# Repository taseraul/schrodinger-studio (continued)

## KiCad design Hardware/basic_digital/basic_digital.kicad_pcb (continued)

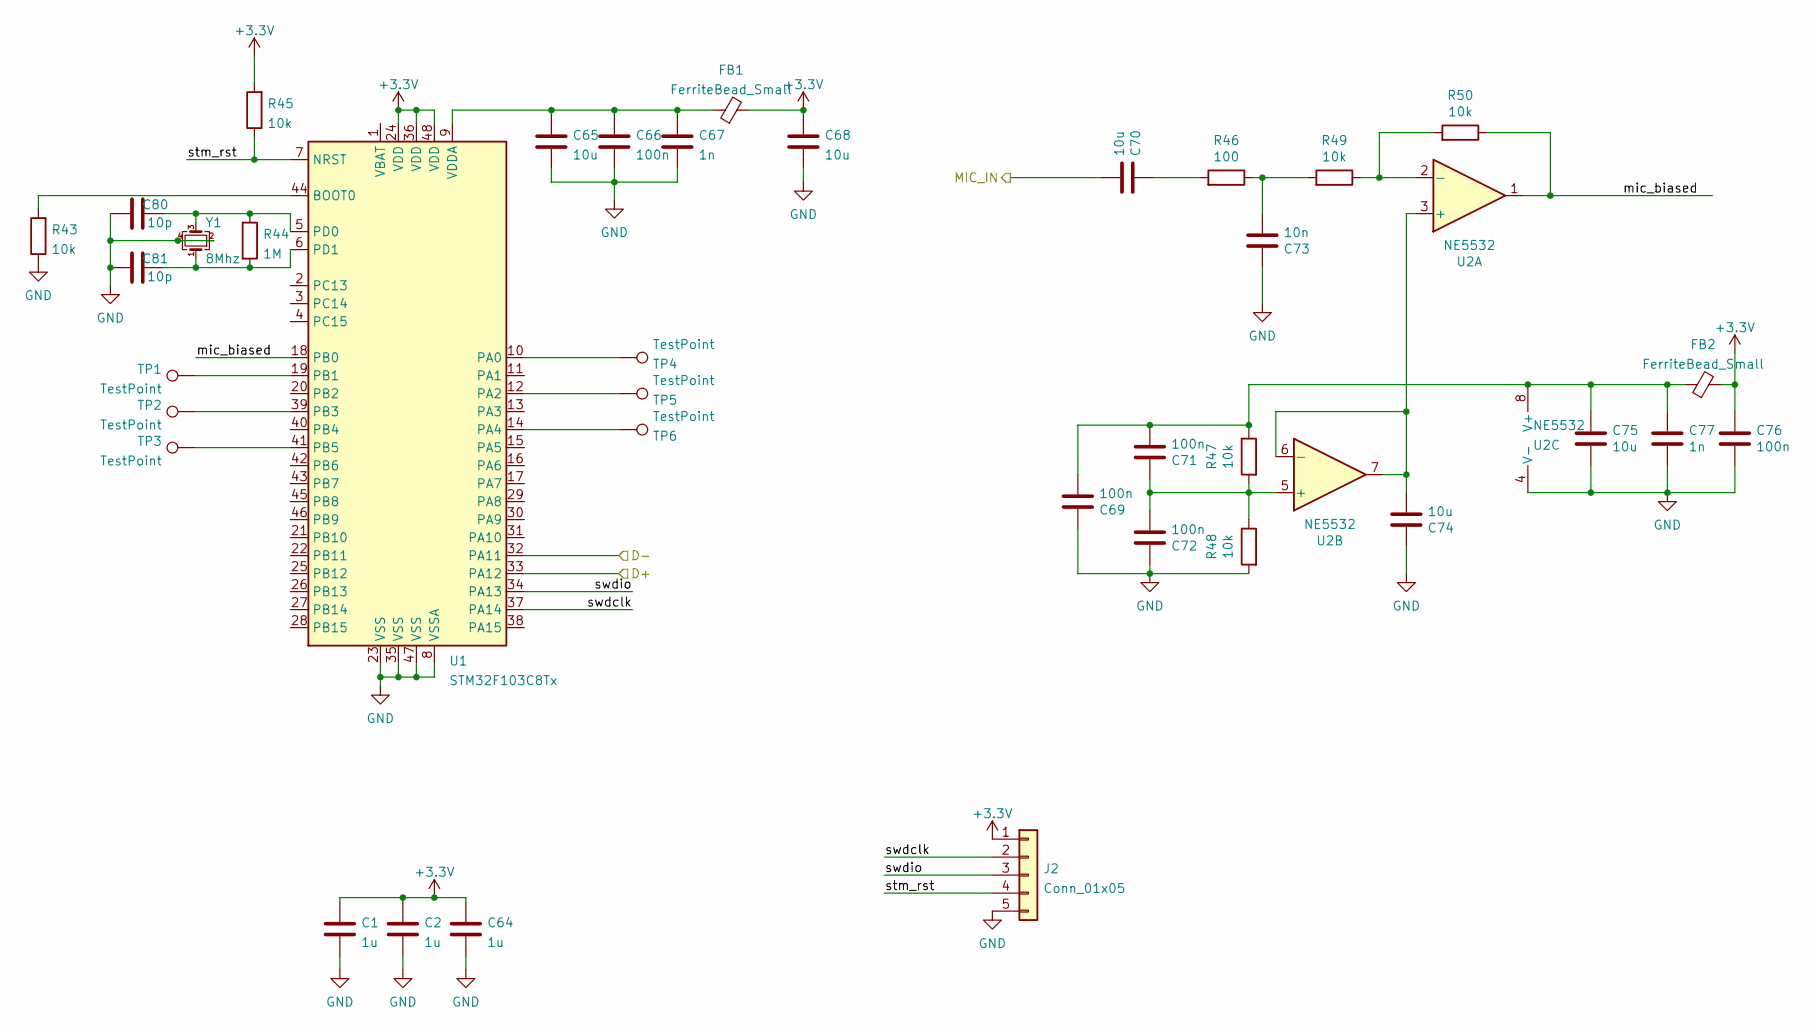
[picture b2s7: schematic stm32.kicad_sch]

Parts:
C1, C2, C64: 1u; C_0603_1608Metric
C65, C68, C70, C74, C75: 10u; C_0603_1608Metric
C66, C69, C71, C72, C76: 100n; C_0603_1608Metric
C67, C77: 1n; C_0603_1608Metric
C73: 10n; C_0603_1608Metric
C80, C81: 10p; C_0603_1608Metric
FB1, FB2: FerriteBead_Small; C_0805_2012Metric
J2: Conn_01x05; PinHeader_1x05_P2.54mm_Vertical
R43, R45, R47, R48, R49, R50: 10k; R_0603_1608Metric
R44: 1M; R_0603_1608Metric
R46: 100; R_0603_1608Metric
TP1, TP2, TP3, TP4, TP5, TP6: TestPoint; TestPoint_Pad_D1.0mm
U1: STM32F103C8Tx; LQFP-48_7x7mm_P0.5mm
U2: NE5532; SOIC-8_3.9x4.9mm_P1.27mm
Y1: 8Mhz; Crystal_SMD_3225-4Pin_3.2x2.5mm

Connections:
+3V3: C1.1, C2.1, C64.1, C68.1, C76.1, FB1.2, FB2.2, J2.1, R45.2, U1.24 (VDD), U1.36 (VDD), U1.48 (VDD); also elsewhere on the board
/power/D+: U1.33 (PA12); also elsewhere on the board
/power/D-: U1.32 (PA11); also elsewhere on the board
/side_con/IN_MONO: C70.2; also elsewhere on the board
/stm32/mic_biased: R50.1, U1.18 (PB0), U2.1
/stm32/stm_rst: J2.4, R45.1, U1.7 (NRST)
/stm32/swdclk: J2.2, U1.37 (PA14)
/stm32/swdio: J2.3, U1.34 (PA13)
unnamed: C65.1, C66.1, C67.1, FB1.1, U1.9 (VDDA)
unnamed: C69.2, C71.2, C75.1, C77.1, FB2.1, R47.1, U2.8 (V+)
unnamed: C70.1, R46.2
unnamed: C71.1, C72.2, R47.2, R48.1, U2.5 (+)
unnamed: C73.2, R46.1, R49.2
unnamed: C74.2, U2.3 (+), U2.6 (-), U2.7
unnamed: C80.2, R44.1, U1.5 (PD0), Y1.3
unnamed: C81.2, R44.2, U1.6 (PD1), Y1.1
unnamed: R43.2, U1.44 (BOOT0)
unnamed: R49.1, R50.2, U2.2 (-)
unnamed: TP1.1, U1.19 (PB1)
unnamed: TP2.1, U1.39 (PB3)
unnamed: TP3.1, U1.41 (PB5)
unnamed: TP4.1, U1.10 (PA0)
unnamed: TP5.1, U1.12 (PA2)
unnamed: TP6.1, U1.14 (PA4)

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
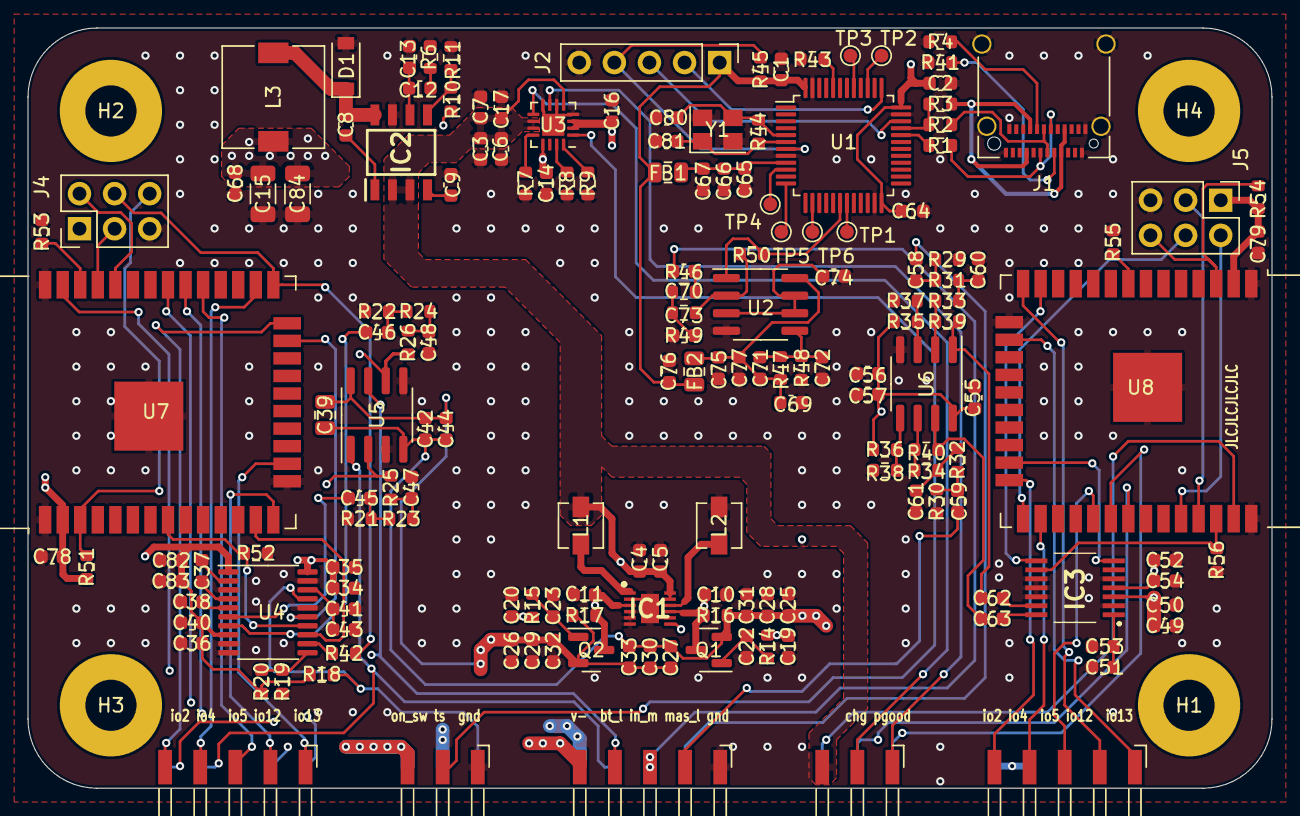
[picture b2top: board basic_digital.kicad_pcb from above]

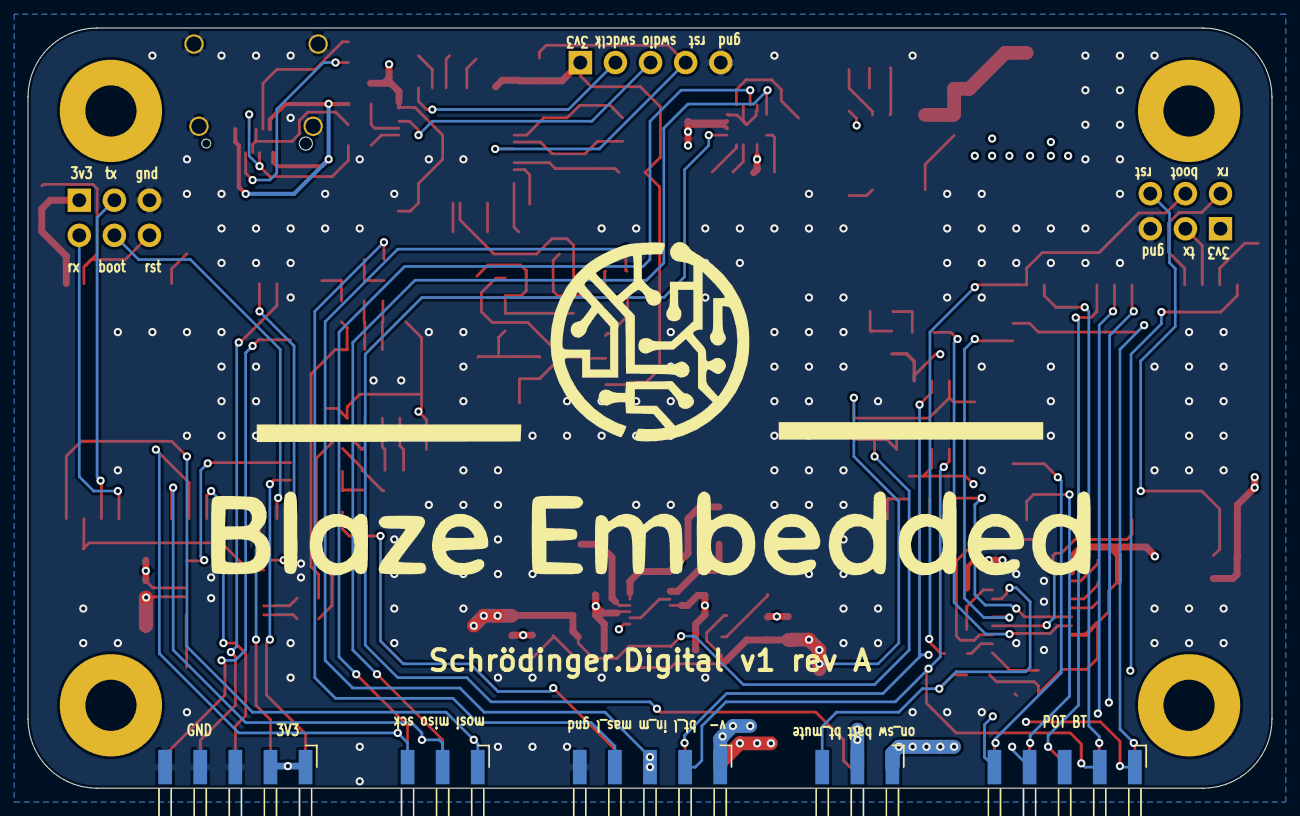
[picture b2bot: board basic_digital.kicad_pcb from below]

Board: 4 copper layers, 90.0 x 55.0 mm, 176 parts (5 on the bottom side), 114 nets.

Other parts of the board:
C78: 1u; C_0603_1608Metric
J4: Conn_01x06; PinHeader_2x03_P2.54mm_Vertical
J9: Conn_01x05; Harwin_M20-89005xx_1x05_P2.54mm_Horizontal
R51: 10k; R_0603_1608Metric
R52, R53: 100k/NC; R_0603_1608Metric
U7: ESP32-WROOM-32

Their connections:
+3V3: C78.1, J4.1, R51.2, U7.2 (VDD); also elsewhere on the board
/bt_in/BCK: U7.13 (IO14); also elsewhere on the board
/bt_in/I2S_IN: R53.2, U7.36 (IO22)
/bt_in/I2S_OUT: R52.2, U7.8 (IO32); also elsewhere on the board
/bt_in/MISO: U7.31 (IO19); also elsewhere on the board
/bt_in/MOSI: U7.37 (IO23); also elsewhere on the board
/bt_in/SCK: U7.30 (IO18); also elsewhere on the board
/bt_in/WS: U7.23 (IO15); also elsewhere on the board
/bt_in/boot: J4.4, U7.25 (IO0); also elsewhere on the board
/bt_in/cs1: J9.3, U7.29 (IO5)
/bt_in/cs2: J9.4, U7.26 (IO4)
/bt_in/io2: J9.5, U7.24 (IO2)
/bt_in/io12: J9.2, U7.14 (IO12)
/bt_in/io13: J9.1, U7.16 (IO13)
/bt_in/rst: J4.6, R51.1, U7.3 (EN)
/bt_in/rx: J4.2, U7.34 (RXD0/IO3)
/bt_in/tx: J4.3, U7.35 (TXD0/IO1)

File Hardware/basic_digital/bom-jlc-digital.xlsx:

Id | Designator | Package | Quantity | Designation | Supplier and ref | Column1 | _1
2 | FB2,FB1 | C_0805_2012Metric | C1017 | FerriteBead_Small
3 | R23,R24,R31,R32,R46 | R_0603_1608Metric | C22775 | 100
4 | C52,C20,C25,C45,C5,C34,C3,C74,C26,C82,C59,C68,C75,C23,C27,C58,C70,C65,C51,C63,C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 | C_0603_1608Metric | C96446 | 10u
6 | U4 | TSSOP-20_4.4x6.5mm_P0.65mm | C107671 | PCM5102
7 | C7,C44,C77,C31,C33,C57,C32,C67 | C_0603_1608Metric | C1588 | 1n
8 | C73,C61,C60,C9,C48,C47 | C_0603_1608Metric | C57112 | 10n
9 | U7,U8 | ESP32-WROOM-32 | C473012 | ESP32-WROOM-32
10 | R34,R40,R54,R37,R33,R43,R35,R18,R48,R51,R39,R45,R10,R47,R49,R36,R38,R50 | R_0603_1608Metric | C25804 | 10k
12 | R52,R56,R55,R53 | C23345 | C23345 | 100k/NC
13 | Q2 | SOT-23 | 1 | BC849
14 | C39 | C_0805_2012Metric | C15850 | 10u/25v
15 | C41,C35,C36,C54,C53,C83,C50 | C_0603_1608Metric | C14663 | 0.1u
16 | Y1 | Crystal_SMD_3225-4Pin_3.2x2.5mm | C242217 | 8Mhz
18 | D1 | D_SOD-123 | C8598 | D_Schottky
20 | R30,R29,R22,R21 | R_0603_1608Metric | C22961 | 220k
21 | Q1 | SOT-23 | 1 | MMBT4403
22 | L1,L2 | L_Vishay_IHLP-1212 | C354574 | 4.7u
23 | C14,C78,C64,C79,C16,C1,C17,C2 | C_0603_1608Metric | C15849 | 1u
24 | R1,R2 | R_0603_1608Metric | C23345 | 20R
25 | C66,C72,C69,C76,C8,C28,C6,C56,C42,C30,C29,C71 | C_0603_1608Metric | C14663 | 100n
26 | IC3 | PCM1808PWR | C55513 | PCM1808PWR
27 | R41,R4,R26,R25 | R_0603_1608Metric | C23186 | 5.1k
29 | U1 | LQFP-48_7x7mm_P0.5mm | 1 | STM32F103C8Tx
30 | R11 | R_0603_1608Metric | C22978 | 3.3k
31 | C37,C38 | C_0603_1608Metric | C23630 | 2.2u
32 | R14,R15 | R_0603_1608Metric | C25819 | 47k
33 | IC1 | SON45P300X300X80-13N-D | C134100 | TPS65133DPDR
34 | R17,R42,R8,R16,R19 | R_0603_1608Metric | C21189 | 0
35 | C15,C84 | C_1206_3216Metric | C96123 | 47u
37 | R6 | R_0603_1608Metric | C22974 | 29.4k
38 | U5,U2,U6 | SOIC-8_3.9x4.9mm_P1.27mm | C7426 | NE5532
39 | R3 | R_0603_1608Metric | C23162 | 4.7k
42 | R44 | R_0603_1608Metric | C22935 | 1M
43 | C12 | C_0603_1608Metric | C1588 | 1000p
44 | L3 | L_7.3x7.3_H4.5 | C354608 | 6.8u
45 | IC2 | SOIC127P600X175-8N | C9865 | TPS54331DR
46 | U3 | VQFN-16-1EP_3x3mm_P0.5mm_EP1.6x1.6mm | C140288 | BQ24072RGT
47 | C13 | C_0603_1608Metric | C1669 | 4.7p
48 | C81,C80 | C_0603_1608Metric | C1634 | 10p
49 | R9,R7 | R_0603_1608Metric | C22975 | 2k
50 | R20 | R_0603_1608Metric | 1 | NC

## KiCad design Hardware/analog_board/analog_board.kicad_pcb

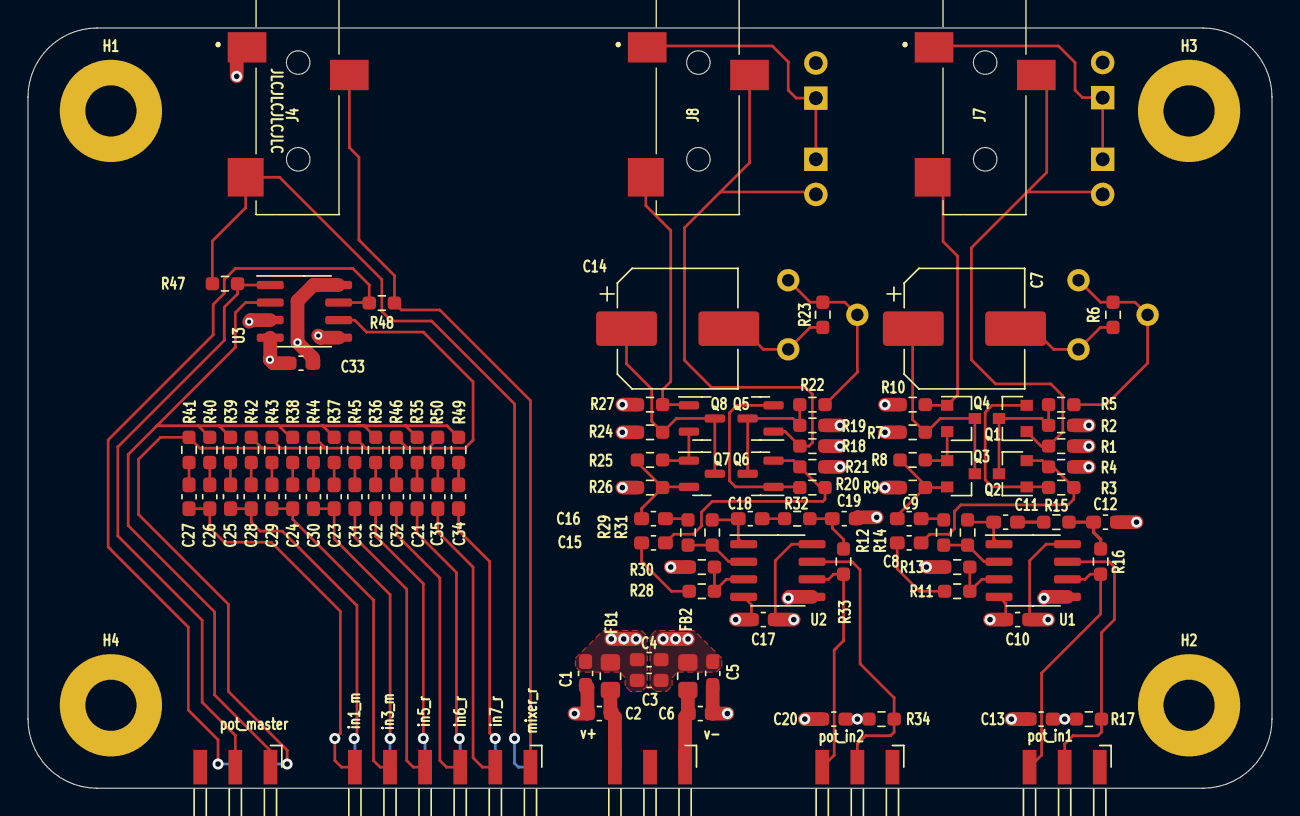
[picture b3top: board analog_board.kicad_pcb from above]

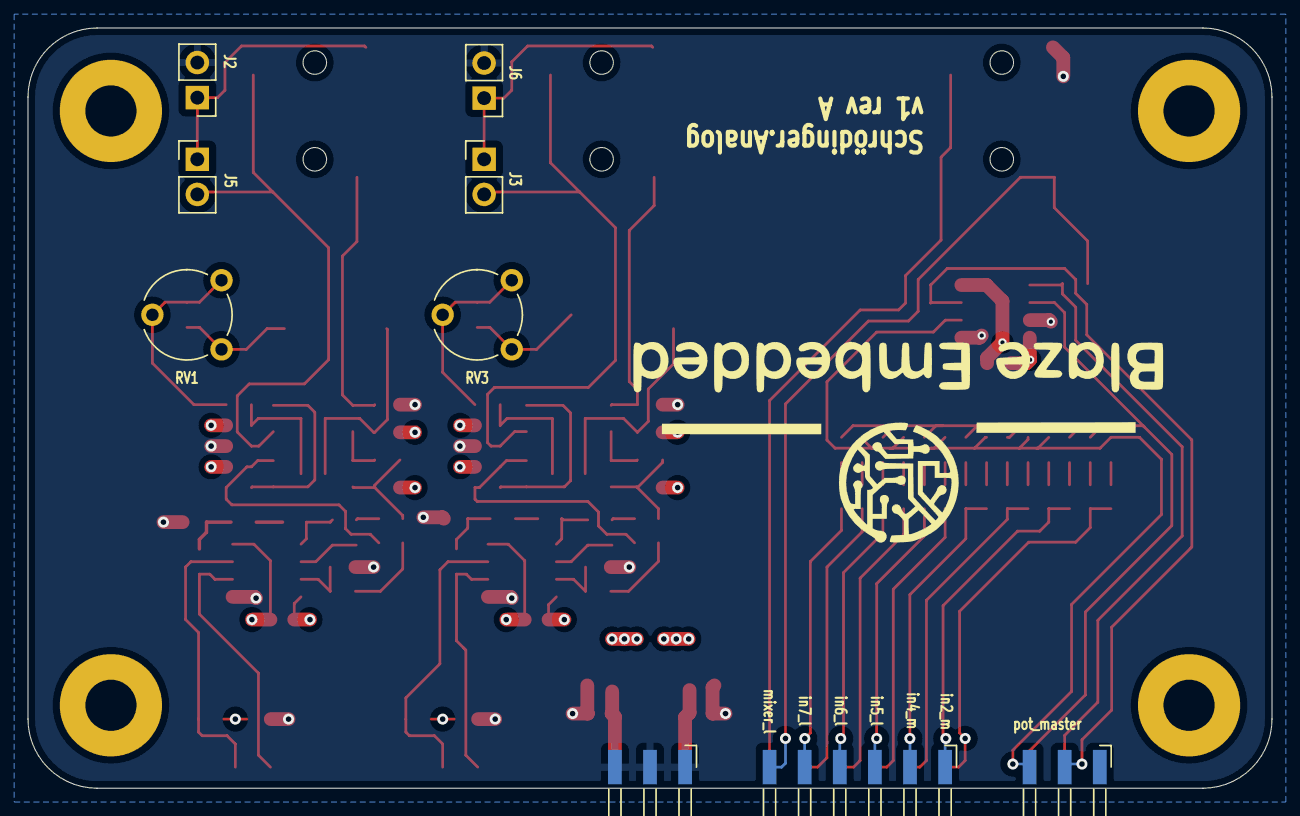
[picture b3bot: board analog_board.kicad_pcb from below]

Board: 4 copper layers, 90.0 x 55.0 mm, 119 parts (9 on the bottom side), 75 nets.

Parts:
C1, C2, C3, C5, C6, C8, C9, C10, C15, C16, C17, C21, C22, C23, C24, C25, C26, C27, C28, C29, C30, C31, C32, C33, C34, C35: 10u; C_0603_1608Metric_Pad1.08x0.95mm_HandSolder
C4: 100n; C_0603_1608Metric_Pad1.08x0.95mm_HandSolder
C7, C14: 1000u; CP_Elec_8x10.5
C11, C18: 1u; C_0603_1608Metric_Pad1.08x0.95mm_HandSolder
C12, C13, C19, C20: 10n; C_0603_1608Metric_Pad1.08x0.95mm_HandSolder
FB1, FB2: FerriteBead_Small; R_0805_2012Metric_Pad1.20x1.40mm_HandSolder
H1, H2, H3, H4: MountingHole_Pad; MountingHole_3.7mm_Pad
J1, J9: Conn_01x06; Harwin_M20-89006xx_1x06_P2.54mm_Horizontal
J2, J3, J5, J6: Conn_01x02; PinHeader_1x02_P2.54mm_Vertical
J4, J7, J8: SJ-3523-SMT-TR; SJ3523SMTTR
J10, J11: Conn_01x03; Harwin_M20-89003xx_1x03_P2.54mm_Horizontal
Q1, Q4, Q5, Q8: MMBT4403; SOT-23
Q2, Q3, Q6, Q7: BC849; SOT-23
R1, R10, R16, R18, R27, R33: 3.3k; R_0603_1608Metric_Pad0.98x0.95mm_HandSolder
R2, R7, R19, R24: 4.7k; R_0603_1608Metric_Pad0.98x0.95mm_HandSolder
R3, R8, R15, R17, R20, R25, R32, R34: 680; R_0603_1608Metric_Pad0.98x0.95mm_HandSolder
R4, R9, R21, R26: 2.2k; R_0603_1608Metric_Pad0.98x0.95mm_HandSolder
R5, R22: 22; R_0603_1608Metric_Pad0.98x0.95mm_HandSolder
R6, R13, R14, R23, R30, R31: 100k; R_0603_1608Metric_Pad0.98x0.95mm_HandSolder
R11, R12, R28, R29: 22k; R_0603_1608Metric_Pad0.98x0.95mm_HandSolder
R35, R36, R37, R38, R39, R40, R41, R42, R43, R44, R45, R46, R49, R50: 5.1k; R_0603_1608Metric_Pad0.98x0.95mm_HandSolder
R47, R48: 100; R_0603_1608Metric_Pad0.98x0.95mm_HandSolder
RV1, RV3: 10k; Potentiometer_Piher_PT-6-V_Vertical
RV2, RV4, RV5, RV6: 10k; Harwin_M20-89003xx_1x03_P2.54mm_Horizontal
U1, U2, U3: NE5532; SOIC-8_3.9x4.9mm_P1.27mm

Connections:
+VDC: C1.2, C3.1, C4.1, C10.1, C17.1, C33.1, FB1.1, R2.1, R7.1, R19.1, R24.1, U1.8 (V+), U2.8 (V+), U3.8 (V+)
-VDC: C3.2, C4.2, C5.1, C10.2, C17.2, C33.2, FB2.2, R4.2, R9.2, R21.2, R26.2, U1.4 (V-), U2.4 (V-), U3.4 (V-)
/Amp1/DIFF+: C9.1, Q3.2 (E), R8.2, R9.1
/Amp1/DIFF-: C8.1, Q2.2 (E), R3.2, R4.1
/Amp1/IN+: J7.2 (TIP), Q4.1 (B), R10.1
/Amp1/IN-: J2.2, J7.3 (RING), Q1.1 (B), R1.1
/Amp2/DIFF+: C16.1, Q7.2 (E), R25.2, R26.1
/Amp2/DIFF-: C15.1, Q6.2 (E), R20.2, R21.1
/Amp2/IN+: J8.2 (TIP), Q8.1 (B), R27.1
/Amp2/IN-: J3.2, J8.3 (RING), Q5.1 (B), R18.1
/IN1_MONO: C13.1, C26.1, C27.1, J1.6, R17.1
/IN2_MONO: C20.1, C25.1, C28.1, J9.1, R34.1
/IN3_MONO: C24.1, C29.1, J1.5
/IN4_MONO: C23.1, C30.1, J9.2
/IN5_L: C22.1, J9.3
/IN5_R: C31.1, J1.4
/IN6_L: C21.1, J9.4
/IN6_R: C32.1, J1.3
/IN7_L: C34.1, J9.5
/IN7_R: C35.1, J1.2
/MIXER_L: J4.2 (TIP), J9.6, R47.1
/MIXER_R: J1.1, J4.3 (RING), R48.1
GND: C1.1, C2.1, C5.2, C6.2, C12.2, C13.2, C19.2, C20.2, J4.1 (SLEEVE), J5.2, J6.2, J11.1, J11.2, J11.3, R1.2, R10.2, R13.2, R18.2, R27.2, R30.2, U1.5 (+), U2.5 (+), U3.3 (+), U3.5 (+)
unnamed: C2.2, FB1.2, J10.3
unnamed: C6.1, FB2.1, J10.1
unnamed: C7.1, Q3.3 (C), Q4.3 (C), R7.2
unnamed: C7.2, R6.2, RV1.3
unnamed: C8.2, R11.1
unnamed: C9.2, R12.1
unnamed: C11.1, R14.1, U1.1
unnamed: C11.2, R15.2
unnamed: C12.1, R15.1, R16.2
unnamed: C14.1, Q7.3 (C), Q8.3 (C), R24.2
unnamed: C14.2, R23.2, RV3.3
unnamed: C15.2, R28.1
unnamed: C16.2, R29.1
unnamed: C18.1, R31.1, U2.1
unnamed: C18.2, R32.2
unnamed: C19.1, R32.1, R33.2
unnamed: C21.2, R35.2
unnamed: C22.2, R36.2
unnamed: C23.2, R37.2
unnamed: C24.2, R38.2
unnamed: C25.2, R39.2
unnamed: C26.2, R40.2
unnamed: C27.2, R41.2
unnamed: C28.2, R42.2
unnamed: C29.2, R43.2
unnamed: C30.2, R44.2
unnamed: C31.2, R45.2
unnamed: C32.2, R46.2
unnamed: C34.2, R49.2
unnamed: C35.2, R50.2
unnamed: J2.1, J5.1, J7.1 (SLEEVE)
unnamed: J3.1, J6.1, J8.1 (SLEEVE)
unnamed: Q1.2 (E), Q2.1 (B), R3.1
unnamed: Q1.3 (C), Q2.3 (C), R2.2, R5.1
unnamed: Q3.1 (B), Q4.2 (E), R8.1
unnamed: Q5.2 (E), Q6.1 (B), R20.1
unnamed: Q5.3 (C), Q6.3 (C), R19.2, R22.1
unnamed: Q7.1 (B), Q8.2 (E), R25.1
unnamed: R5.2, R6.1, RV1.1, RV1.2
unnamed: R11.2, R13.1, U1.3 (+)
unnamed: R12.2, R14.2, U1.2 (-)
unnamed: R16.1, RV2.3, U1.6 (-)
unnamed: R17.2, RV2.2, U1.7
unnamed: R22.2, R23.1, RV3.1, RV3.2
unnamed: R28.2, R30.1, U2.3 (+)
unnamed: R29.2, R31.2, U2.2 (-)
unnamed: R33.1, RV4.3, U2.6 (-)
unnamed: R34.2, RV4.2, U2.7
unnamed: R35.1, R36.1, R37.1, R38.1, R39.1, R40.1, R49.1, RV5.1, U3.2 (-)
unnamed: R41.1, R42.1, R43.1, R44.1, R45.1, R46.1, R50.1, RV6.3, U3.6 (-)
unnamed: R47.2, RV5.2, U3.1
unnamed: R48.2, RV6.2, U3.7

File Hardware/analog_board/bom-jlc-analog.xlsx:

Comment | Designator | Footprint | JLC
5.1k | R50,R49,R37,R38,R39,R40,R41,R42,R43,R44,R36,R35,R45,R46 | R_0603_1608Metric_Pad0.98x0.95mm_HandSolder | C23186
10u | C35,C34,C33,C10,C9,C8,C25,C30,C2,C1,C26,C5,C6,C15,C24,C31,C3,C22,C29,C27,C32,C1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 | C_0603_1608Metric_Pad1.08x0.95mm_HandSolder | C96446
100 | R47,R48 | R_0603_1608Metric_Pad0.98x0.95mm_HandSolder | C22775
NE5532 | U3,U1,U2 | SOIC-8_3.9x4.9mm_P1.27mm | C7426
MMBT4403 | Q1,Q4,Q8,Q5 | SOT-23
4.7k | R7,R2,R24,R19 | R_0603_1608Metric_Pad0.98x0.95mm_HandSolder | C23162
680 | R8,R3,R32,R15,R17,R34,R20,R25 | R_0603_1608Metric_Pad0.98x0.95mm_HandSolder | C23228
3.3k | R10,R1,R16,R33,R27,R18 | R_0603_1608Metric_Pad0.98x0.95mm_HandSolder | C22978
2.2k | R9,R4,R26,R21 | R_0603_1608Metric_Pad0.98x0.95mm_HandSolder | C4190
22 | R5,R22 | R_0603_1608Metric_Pad0.98x0.95mm_HandSolder | C23345
1000u | C7,C14 | CP_Elec_8x10.5
100k | R14,R6,R13,R23,R30,R31 | R_0603_1608Metric_Pad0.98x0.95mm_HandSolder | C25803
22k | R11,R12,R29,R28 | R_0603_1608Metric_Pad0.98x0.95mm_HandSolder | C31850
1u | C11,C18 | C_0603_1608Metric_Pad1.08x0.95mm_HandSolder | C15849
BC849 | Q2,Q3,Q7,Q6 | SOT-23
10n | C13,C20,C12,C19 | C_0603_1608Metric_Pad1.08x0.95mm_HandSolder | C57112
FerriteBead_Small | FB2,FB1 | R_0805_2012Metric_Pad1.20x1.40mm_HandSolder | C1017
100n | C4 | C_0603_1608Metric_Pad1.08x0.95mm_HandSolder | C14663

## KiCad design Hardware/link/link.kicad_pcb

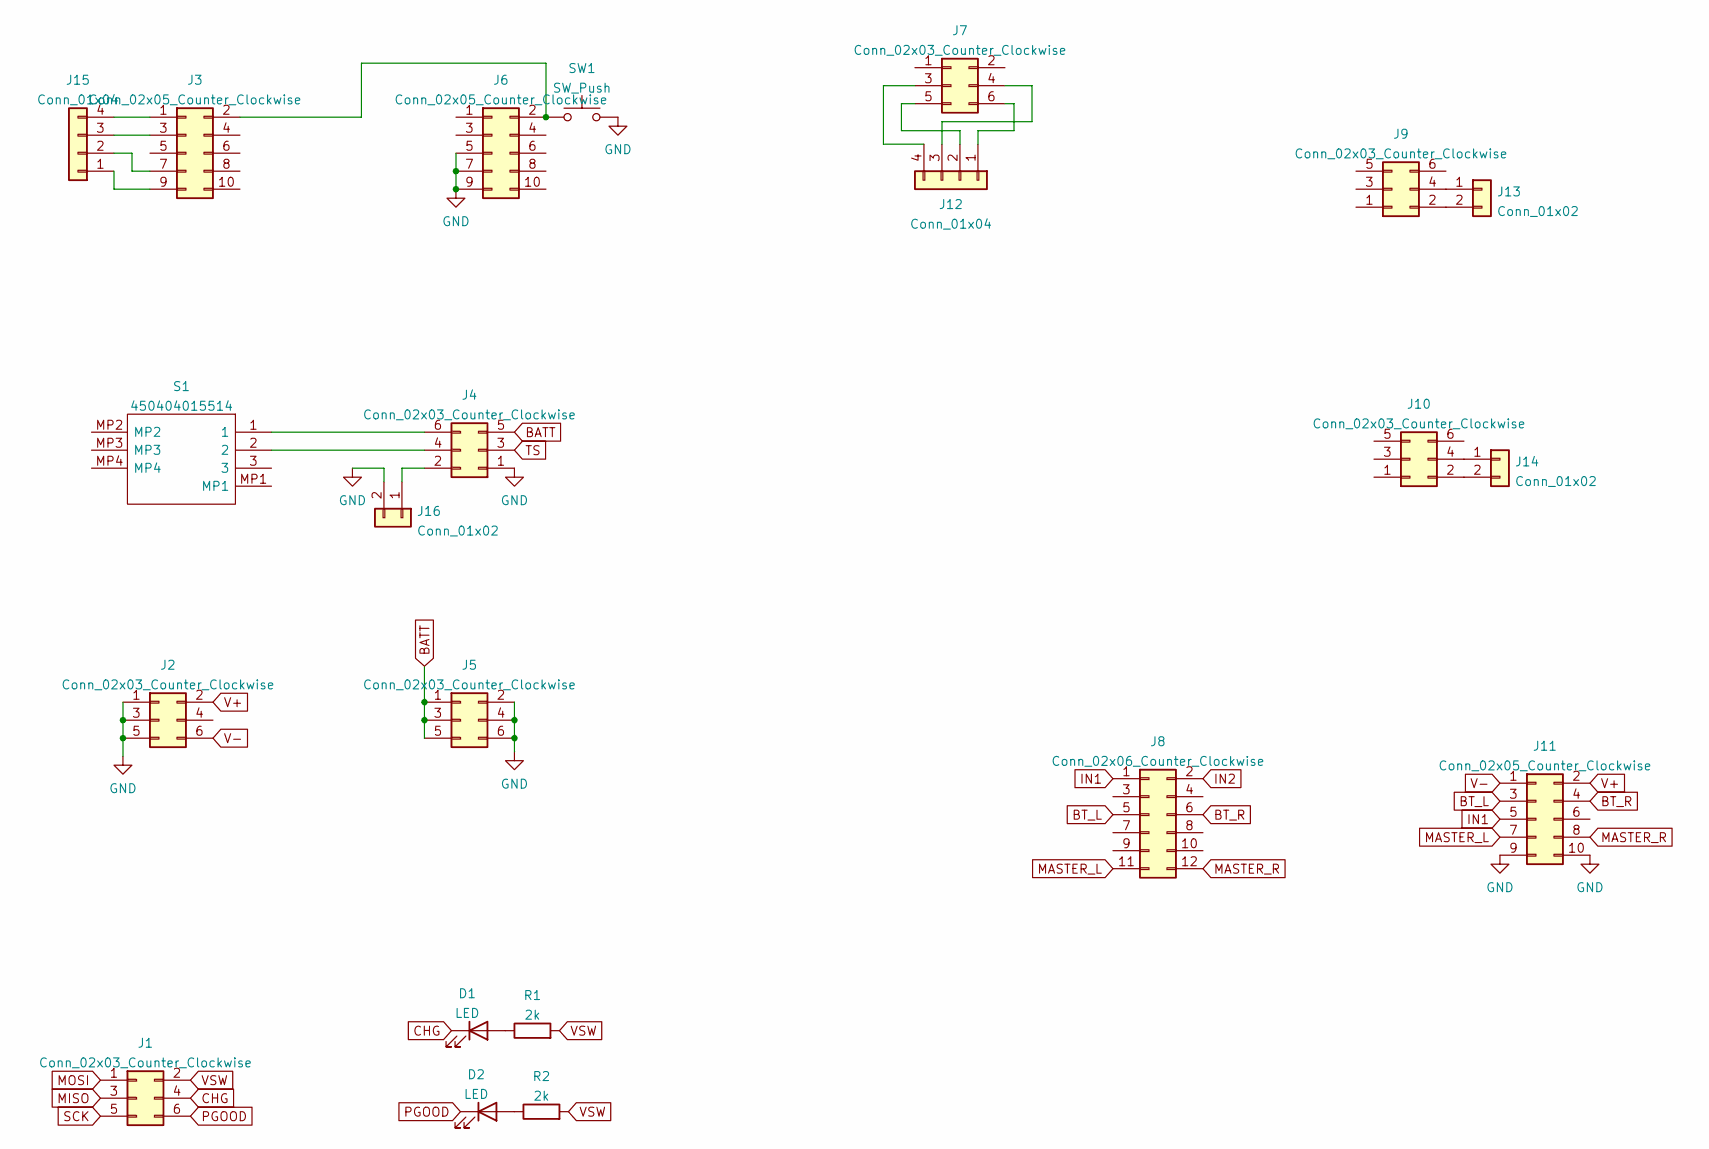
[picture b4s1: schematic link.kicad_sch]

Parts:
D1, D2: LED; LED_D5.0mm
J1, J2, J4, J5, J7, J9, J10: Conn_02x03_Counter_Clockwise; PinSocket_2x03_P2.54mm_Vertical
J3, J6, J11: Conn_02x05_Counter_Clockwise; PinSocket_2x05_P2.54mm_Vertical
J8: Conn_02x06_Counter_Clockwise; PinSocket_2x06_P2.54mm_Vertical
J12, J15: Conn_01x04; PinHeader_1x04_P2.54mm_Vertical
J13, J14, J16: Conn_01x02; PinHeader_1x02_P2.54mm_Vertical
R1, R2: 2k; R_0603_1608Metric
S1: 450404015514; Mouser Part Number 710-450404015514
SW1: SW_Push; SW_Tactile_SKHH_Angled

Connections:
BATT: J4.5, J5.1, J5.3, J5.5
BT_L: J8.5, J11.3
BT_R: J8.6, J11.4
CHG: D1.1 (K), J1.4
GND: J2.1, J2.3, J2.5, J4.1, J5.2, J5.4, J5.6, J6.5, J6.7, J6.9, J11.9, J11.10, J16.2, SW1.2
IN1: J8.1, J11.5
IN2: J8.2
MASTER_L: J8.11, J11.7
MASTER_R: J8.12, J11.8
MISO: J1.3
MOSI: J1.1
unnamed: D1.2 (A), R1.1
unnamed: D2.2 (A), R2.1
unnamed: J3.1, J15.4
unnamed: J3.2, J6.2, SW1.1
unnamed: J3.3, J15.3
unnamed: J3.7, J15.2
unnamed: J3.9, J15.1
unnamed: J4.2, J16.1
unnamed: J4.4, S1.2
unnamed: J4.6, S1.1
unnamed: J10.2, J14.2
unnamed: J10.4, J14.1
unnamed: J7.6, J12.1
unnamed: J7.5, J12.2
unnamed: J7.4, J12.3
unnamed: J7.3, J12.4
unnamed: J9.4, J13.1
unnamed: J9.2, J13.2
PGOOD: D2.1 (K), J1.6
SCK: J1.5
TS: J4.3
V+: J2.2, J11.2
V-: J2.6, J11.1
VSW: J1.2, R1.2, R2.2

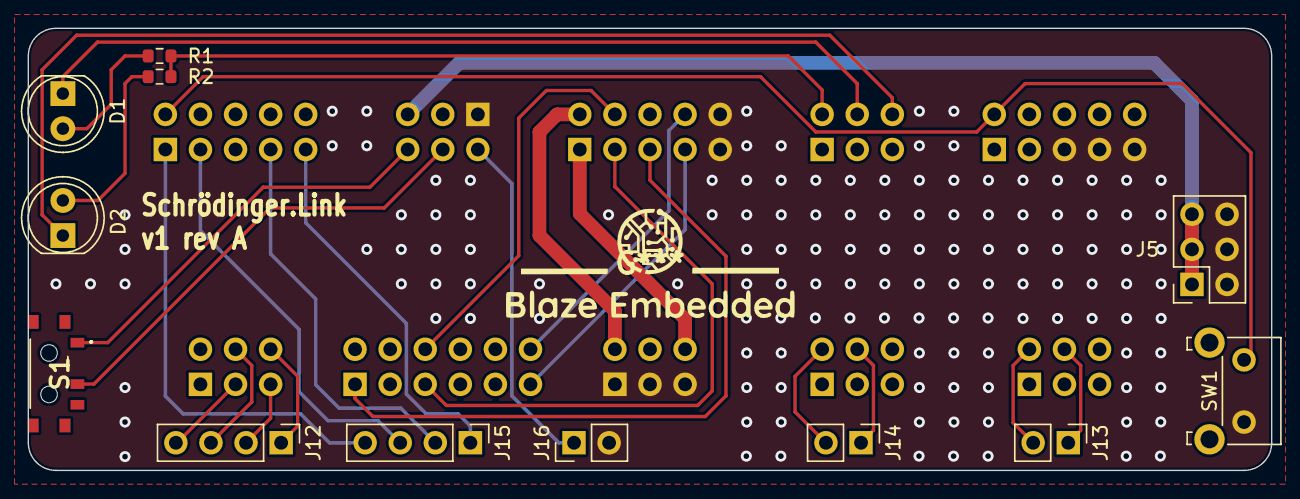
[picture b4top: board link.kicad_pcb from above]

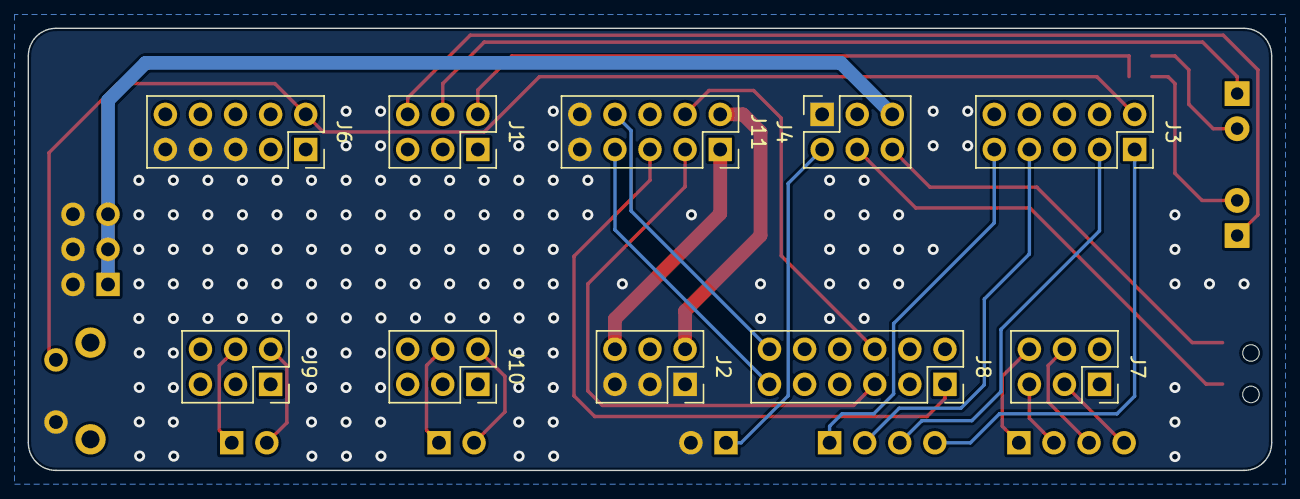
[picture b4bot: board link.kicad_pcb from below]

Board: 2 copper layers, 90.0 x 32.0 mm, 22 parts (10 on the bottom side), 30 nets.

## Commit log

2022-11-26 Mood redisign + code
2022-12-23 Mood complete, working on fft webpage
2023-06-22 add mood case v2
2023-06-25 new light generation algorithm
2023-12-20 Unified control via webpage - main unit
2023-12-27 tweak mood for multichannel neopixel controller
2023-12-30 light parameter tweaks
2023-12-30 try 2 light algo
2025-06-15 Initial commit with switch to parallel tasks
2025-06-15 Fix bt and wifi coexistence
2025-06-16 circular buffer try1
2025-06-16 test-fft2
2025-06-16 Create circular buffer between bt and fft
2025-06-17 improve fft performance
2025-06-17 FFT visualisation in webserver
2025-06-20 fft visualization improvements
2025-08-17 Remove OTA
2025-08-17 Refactor
2025-09-04 manual refactor after ai
2025-09-11 Bt i2s echo as buffer
